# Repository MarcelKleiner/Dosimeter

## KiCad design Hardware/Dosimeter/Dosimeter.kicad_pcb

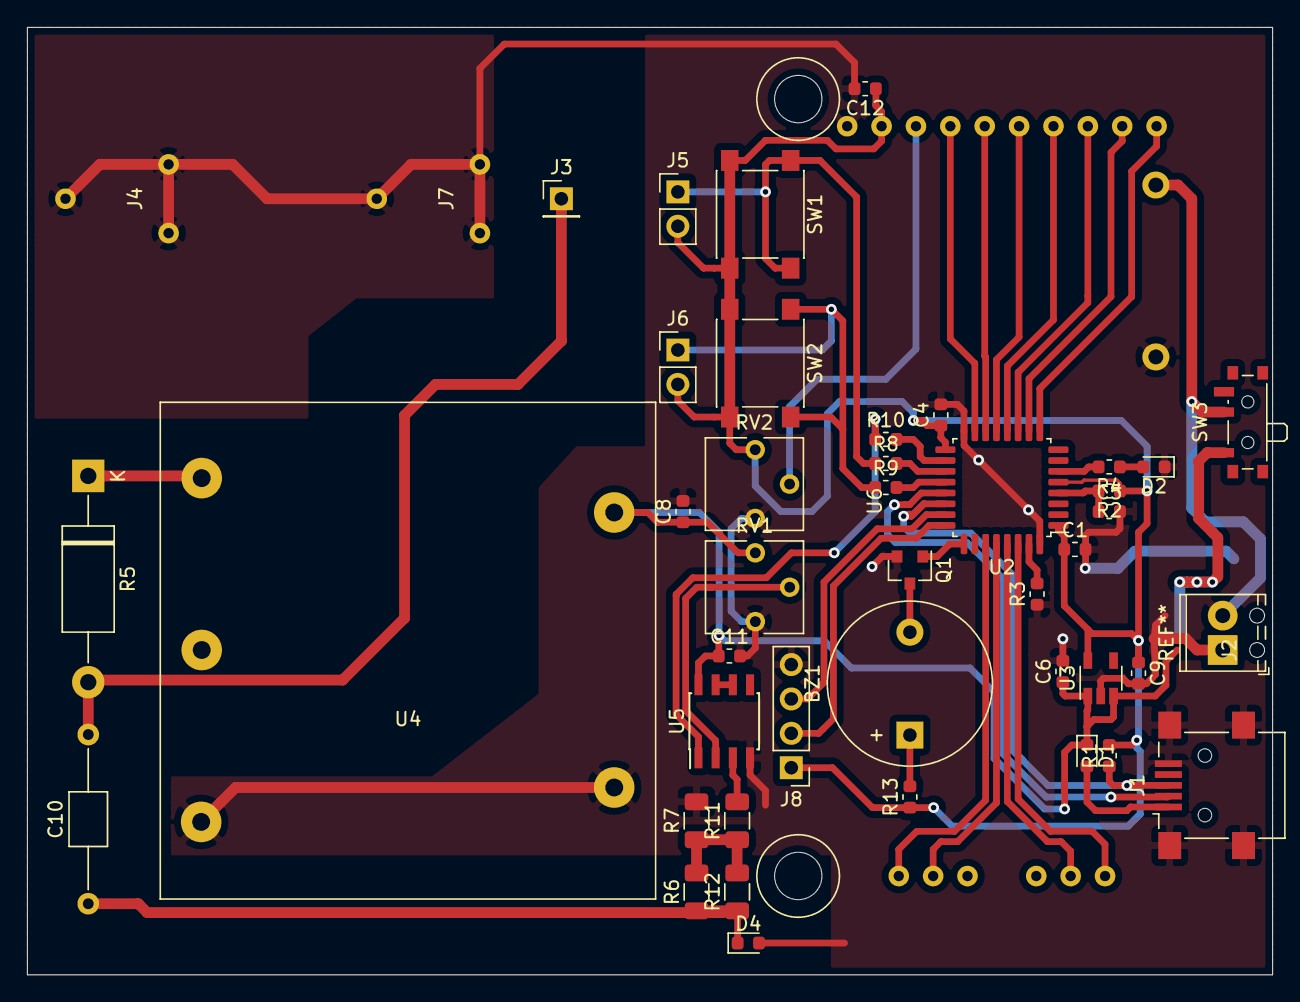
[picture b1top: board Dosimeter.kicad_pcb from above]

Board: 2 copper layers, 92.0 x 70.0 mm, 46 parts (1 on the bottom side), 41 nets.

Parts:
BT1: Battery; BatteryHolder_Keystone_2477_4xAA
BZ1: Buzzer; Buzzer_12x9.5RM7.6
C1, C4, C5, C6, C9, C11, C12: 100n; C_0603_1608Metric
C8: C; C_0603_1608Metric
C10: 100p; C_Axial_L3.8mm_D2.6mm_P12.50mm_Horizontal
D1: D; D_0603_1608Metric
D2: LED; LED_0603_1608Metric
D4: D_TVS; D_0603_1608Metric
J1: USB_B_Mini; USB_Mini-B_Lumberg_2486_01_Horizontal
J2: Vin +12; TerminalBlock_Phoenix_MPT-0,5-2-2.54_1x02_P2.54mm_Horizontal
J3: Conn_01x01_Female; PinHeader_1x01_P2.54mm_Vertical
J4, J7: Conn_01x01_Female; 54_keystone_16-19mm
J5, J6: Conn_01x02_Male; PinHeader_1x02_P2.54mm_Vertical
J8: Conn_01x04_Male; PinHeader_1x04_P2.54mm_Vertical
Q1: BC846; SOT-23
R1: 1.5k; R_0603_1608Metric
R2, R3: 100k; R_0603_1608Metric
R4, R8, R9, R13: 240; R_0603_1608Metric
R5: 100M; D_DO-15_P15.24mm_Horizontal
R6: 1M; R_1206_3216Metric
R7, R11: 200k; R_1206_3216Metric
R10: R; R_0603_1608Metric
R12: 0; R_1206_3216Metric
RV1, RV2: R_POT; Potentiometer_Vishay_T73YP_Vertical
SW1, SW2: SW_Push; SW_SPST_PTS645
SW3: SW_SPST; SW_SPDT_PCM12
U2: STM32L412K8Tx; LQFP-32_7x7mm_P0.8mm
U3: NCP718BSN330T1G; TSOT-23-5
U4: G40
U5: TL072; SOIC-8_3.9x4.9mm_P1.27mm
U6: LCD_NHD-0108CZ; LCD_NHD_0108CZ

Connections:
+3V3: C1.1, C4.1, C9.1, C12.1, J5.2, J6.2, J8.1, R1.2, R2.1, R13.1, RV2.3, SW1.2, SW2.2, U2.1, U2.5, U2.17, U3.5, U6.2
+5V: D1.2, J1.1
+6V: C6.1, C8.1, C11.1, D1.1, RV1.3, SW3.1, U3.1, U3.3, U4.1, U5.8
+VDC: R5.1, U4.3
/COUNTER_OUT: R10.2, U2.18
/D+: J1.3, R1.1, U2.22
/D-: J1.2, U2.21
/DB0: U2.27, U6.11
/DB1: U2.28, U6.12
/DB2: U2.29, U6.13
/DB3: U2.30, U6.14
/DB4: U2.12, U6.7
/DB5: U2.11, U6.8
/DB6: U2.10, U6.9
/DB7: U2.9, U6.10
/E: U2.13, U6.6
/RS: U2.15, U6.4
/R_W: U2.14, U6.5
/SW1: R8.2, U2.19
/SW2: R9.2, U2.20
GND: BT1.2, C1.2, C4.2, C5.2, C6.2, C8.2, C9.2, C11.2, C12.2, D2.1, D4.2, J1.5, J1.6, J2.1, J4.1, J7.1, J8.4, Q1.2, R3.1, R7.2, RV1.1, RV2.1, U2.16, U2.32, U3.2, U4.2, U4.4, U5.4, U6.1
unnamed: BT1.1, J2.2, SW3.2
unnamed: BZ1.1, R13.2
unnamed: BZ1.2, Q1.3
unnamed: C5.1, R2.2, U2.4
unnamed: C10.1, D4.1, R6.1, R12.1
unnamed: C10.2, J3.1, R5.2
unnamed: D2.2, R4.1
unnamed: J5.1, R8.1, SW1.1
unnamed: J6.1, R9.1, SW2.1
unnamed: Q1.1, U2.25
unnamed: R3.2, U2.31
unnamed: R4.2, U2.6
unnamed: R10.1, U5.1
unnamed: R6.2, R7.1, R11.1, R12.2
unnamed: R11.2, U5.3
unnamed: RV1.2, U5.2
unnamed: RV2.2, U6.3
unnamed: U5.6, U5.7
SWCLK: J8.2, U2.24
SWDIO: J8.3, U2.23

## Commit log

2020-08-29 initialcommit
2020-08-30 complete HW, add Software
2020-08-31 update software LCD
2020-08-31 add LCD Test F303
2020-09-03 update hardware (add switch)
2020-09-04 update Hardware
